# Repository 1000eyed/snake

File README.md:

# Snake

A semi-ortholinear keyboard with LEDs, rotary encoder support and spacebar options.

## How to build one

Very easy project.

### Part list
| #     | name                 | comments                                  |
|-------|----------------------|-------------------------------------------|
| 1     | main PCB             | Order at fabricator of your choice (ouch, expensive!)        |
| 42    | hotswap sockets      | Whatever you are into                 |
| 42    | switches             | MX compatible                        |
| 42    | Keycaps              | MX-compatible                         |
| 1     | Rotary Encoder       | optional                             |
| NA    | Rubber cord D3.53 mm |  https://www.amazon.de/-/en/SHOCRE-Rubber-Gasket-Nitrile-Diameter/dp/B0CGDMGRZM      |

- Solder the sockets to the PCB according to chosen layout. 
- Mount stabilizers. Note: depending on the layout you [i]may[/i] need to file just a tad the stabilizer lips, so they clear the diodes. If they do not seem to fit, do not force them into place, inspect and file if needed!
- Mount the plate to the PCB and secure it with switches in the corners. 
- Mount all other switches.
- Cut and insert cord pieces into the pockets between the PCB and the plate.
- Insert the assembly into the case. Start with the USB side.

### Firmware

- Install WinUSB driver, using Zadig (https://github.com/qmk/qmk_firmware/blob/master/docs/driver_installation_zadig.md)
- Flash the firmware onto the board. Bootloader mode: hold top left key while plugging in. I used QMK Toolbox (https://qmk.fm/toolbox).

### Done

Enjoy your Snake!

## Acknowledgements

Joe Scotto for publishing the STM32 Scottomodule (https://www.youtube.com/joe_scotto). 
Theycallmeboxy for case inspirations (https://github.com/theycallmeboxy/bassik).

## Gallery

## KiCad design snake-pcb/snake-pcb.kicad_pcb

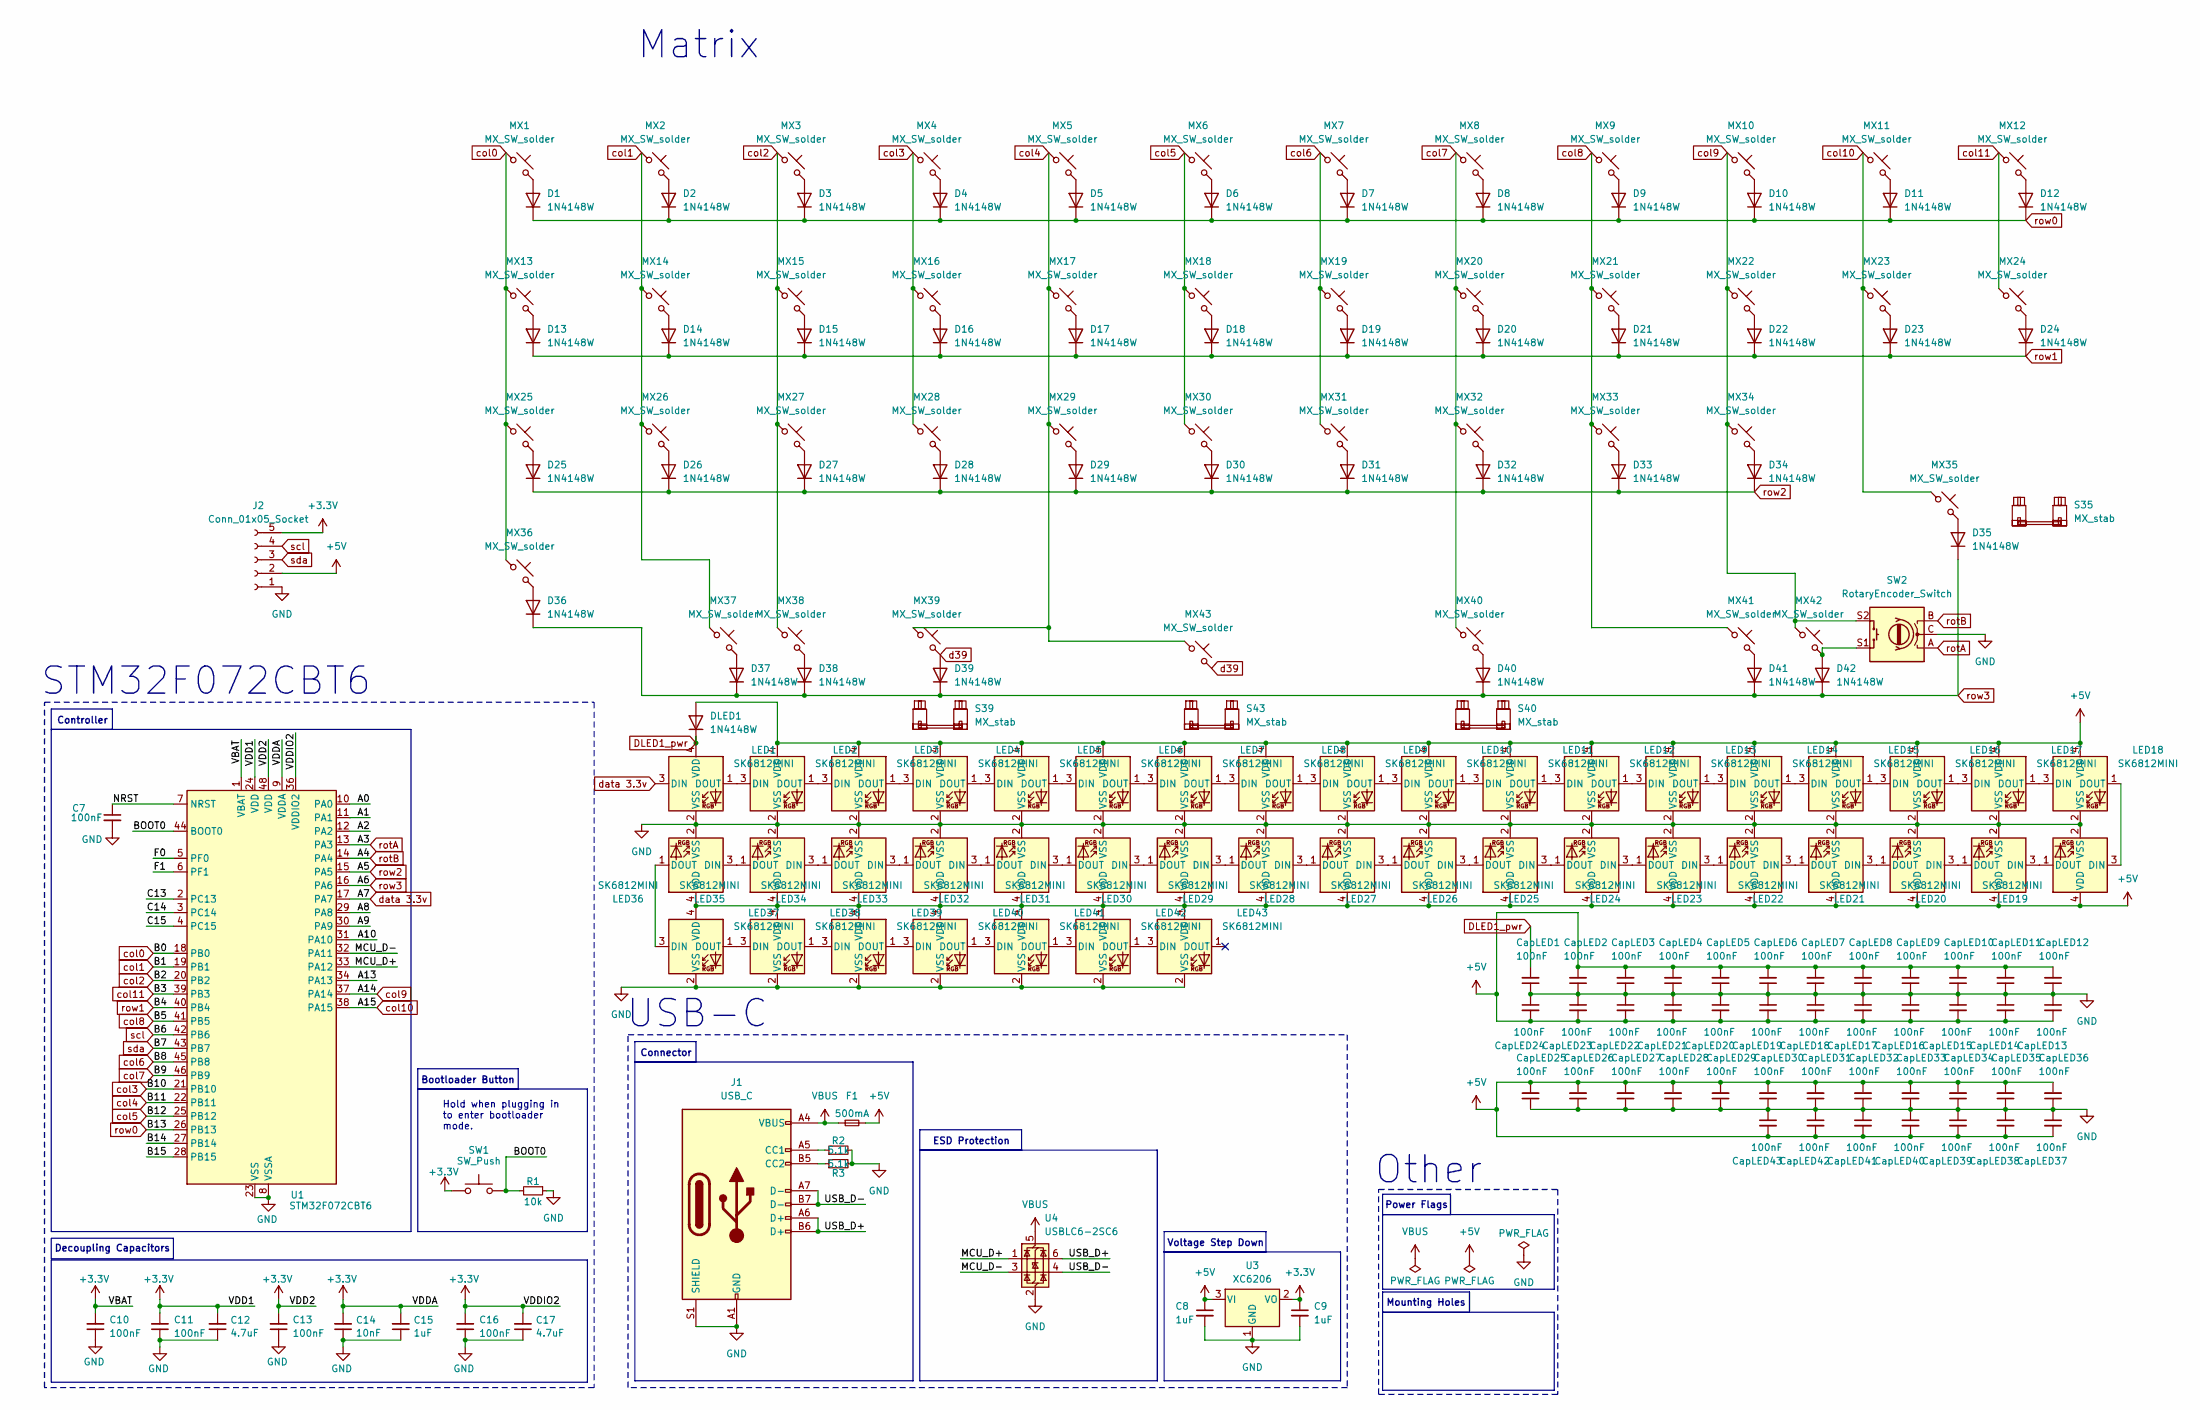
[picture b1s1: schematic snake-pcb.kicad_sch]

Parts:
C7: 100nF; Capacitor_0402; LCSC C307331
C8, C9: 1uF; Capacitor_0402; LCSC C52923
C10, C11, C13, C16: 100nF; Capacitor_0402; MPN CL05B104KB54PNC; LCSC C307331
C12, C17: 4.7uF; Capacitor_0402; MPN CL05A475MP5NRNC; LCSC C23733
C14: 10nF; Capacitor_0402; MPN CL05B103KB5NNNC; LCSC C15195
C15: 1uF; Capacitor_0402; MPN CL05A105KA5NQNC; LCSC C52923
CapLED1, CapLED2, CapLED3, CapLED4, CapLED5, CapLED6, CapLED7, CapLED8, CapLED9, CapLED10, CapLED11, CapLED12, CapLED13, CapLED14, CapLED15, CapLED16, CapLED17, CapLED18, CapLED19, CapLED20, CapLED21, CapLED22, CapLED23, CapLED24, CapLED25, CapLED26, CapLED27, CapLED28, CapLED29, CapLED30, CapLED31, CapLED32, CapLED33, CapLED34, CapLED35, CapLED36, CapLED37, CapLED38, CapLED39, CapLED40, CapLED41, CapLED42, CapLED43: 100nF; Capacitor_0402; MPN CL05B104KB54PNC; LCSC C307331
D1, D2, D3, D4, D5, D6, D7, D8, D9, D10, D11, D12, D13, D14, D15, D16, D17, D18, D19, D20, D21, D22, D23, D24, D25, D26, D27, D28, D29, D30, D31, D32, D33, D34, D35, D36, D37, D38, D39, D40, D41, D42: 1N4148W; D_SOD-123
DLED1: 1N4148W; D_SOD-123
F1: 500mA; Fuse_0603; LCSC C210357
J1: USB_C; USB_C_HRO_TYPE-C-31-M-12; LCSC C165948
J2: Conn_01x05_Socket; JST_EH_B5B-EH-A_1x05_P2.50mm_Vertical
LED1, LED2, LED3, LED4, LED5, LED6, LED7, LED8, LED9, LED10, LED11, LED12, LED13, LED14, LED15, LED16, LED17, LED18, LED19, LED20, LED21, LED22, LED23, LED24, LED25, LED26, LED27, LED28, LED29, LED30, LED31, LED32, LED33, LED34, LED35, LED36, LED37, LED38, LED39, LED40, LED41, LED42, LED43: SK6812MINI; LED_SK6812MINI
MX1, MX2, MX3, MX4, MX5, MX6, MX7, MX8, MX9, MX10, MX11, MX12, MX13, MX14, MX15, MX16, MX17, MX18, MX19, MX20, MX21, MX22, MX23, MX24, MX25, MX26, MX27, MX28, MX29, MX30, MX31, MX32, MX33, MX34, MX35, MX37, MX38, MX39, MX40, MX41, MX42, MX43: MX_SW_solder; SW_MX_HS_CPG151101S11_1u
MX36: MX_SW_solder; SW_MX_HS_CPG151101S11_1.25u
R1: 10k; Resistor_0402; LCSC C25744
R2, R3: 5.1k; Resistor_0402; LCSC C25905
S35: MX_stab; STAB_MX_P_ISO-ROT
S39: MX_stab; STAB_MX_P_2.75u
S40: MX_stab; STAB_MX_P_2.25u
S43: MX_stab; STAB_MX_P_7u
SW1: SW_Push; Button_TL3342; LCSC C115351
SW2: RotaryEncoder_Switch; Encoder_EC11_MX
U1: STM32F072CBT6; Package_LQFP-48_7x7mm_P0.5; LCSC C81720
U3: XC6206; Voltage_SOT-23; LCSC C5446
U4: USBLC6-2SC6; ESD_SOT-23-6; LCSC C2827654

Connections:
+3.3V: C9.1, C10.2, C11.2, C12.2, C13.2, C14.2, C15.2, C16.2, C17.2, J2.5, SW1.1, U1.1 (VBAT), U1.9 (VDDA), U1.24 (VDD), U1.36 (VDDIO2), U1.48 (VDD), U3.2 (VO)
+5V: C8.1, CapLED2.2, CapLED3.2, CapLED4.2, CapLED5.2, CapLED6.2, CapLED7.2, CapLED8.2, CapLED9.2, CapLED10.2, CapLED11.2, CapLED12.2, CapLED13.2, CapLED14.2, CapLED15.2, CapLED16.2, CapLED17.2, CapLED18.2, CapLED19.2, CapLED20.2, CapLED21.2, CapLED22.2, CapLED23.2, CapLED24.2, CapLED25.2, CapLED26.2, CapLED27.2, CapLED28.2, CapLED29.2, CapLED30.2, CapLED31.2, CapLED32.2, CapLED33.2, CapLED34.2, CapLED35.2, CapLED36.2, CapLED37.2, CapLED38.2, CapLED39.2, CapLED40.2, CapLED41.2, CapLED42.2, CapLED43.2, DLED1.2 (A), F1.2, J2.2, LED2.4 (VDD), LED3.4 (VDD), LED4.4 (VDD), LED5.4 (VDD), LED6.4 (VDD), LED7.4 (VDD), LED8.4 (VDD), LED9.4 (VDD), LED10.4 (VDD), LED11.4 (VDD), LED12.4 (VDD), LED13.4 (VDD), LED14.4 (VDD), LED15.4 (VDD), LED16.4 (VDD), LED17.4 (VDD), LED18.4 (VDD), LED19.4 (VDD), LED20.4 (VDD), LED21.4 (VDD), LED22.4 (VDD), LED23.4 (VDD), LED24.4 (VDD), LED25.4 (VDD), LED26.4 (VDD), LED27.4 (VDD), LED28.4 (VDD), LED29.4 (VDD), LED30.4 (VDD), LED31.4 (VDD), LED32.4 (VDD), LED33.4 (VDD), LED34.4 (VDD), LED35.4 (VDD), LED36.4 (VDD), LED37.4 (VDD), LED38.4 (VDD), LED39.4 (VDD), LED40.4 (VDD), LED41.4 (VDD), LED42.4 (VDD), LED43.4 (VDD), U3.3 (VI)
/A0: U1.10 (PA0)
/A1: U1.11 (PA1)
/A2: U1.12 (PA2)
/A8: U1.29 (PA8)
/A9: U1.30 (PA9)
/A10: U1.31 (PA10)
/A13: U1.34 (PA13)
/B14: U1.27 (PB14)
/B15: U1.28 (PB15)
/BOOT0: R1.2, SW1.2, U1.44 (BOOT0)
/C13: U1.2 (PC13)
/C14: U1.3 (PC14)
/C15: U1.4 (PC15)
/F0: U1.5 (PF0)
/F1: U1.6 (PF1)
/MCU_D+: U1.33 (PA12), U4.1 (I/O1)
/MCU_D-: U1.32 (PA11), U4.3 (I/O2)
/NRST: C7.1, U1.7 (NRST)
/USB_D+: J1.A6 (D+), J1.B6 (D+), U4.6 (I/O1)
/USB_D-: J1.A7 (D-), J1.B7 (D-), U4.4 (I/O2)
DLED1_pwr: CapLED1.2, DLED1.1 (K), LED1.4 (VDD)
GND: C7.2, C8.2, C9.2, C10.1, C11.1, C12.1, C13.1, C14.1, C15.1, C16.1, C17.1, CapLED1.1, CapLED2.1, CapLED3.1, CapLED4.1, CapLED5.1, CapLED6.1, CapLED7.1, CapLED8.1, CapLED9.1, CapLED10.1, CapLED11.1, CapLED12.1, CapLED13.1, CapLED14.1, CapLED15.1, CapLED16.1, CapLED17.1, CapLED18.1, CapLED19.1, CapLED20.1, CapLED21.1, CapLED22.1, CapLED23.1, CapLED24.1, CapLED25.1, CapLED26.1, CapLED27.1, CapLED28.1, CapLED29.1, CapLED30.1, CapLED31.1, CapLED32.1, CapLED33.1, CapLED34.1, CapLED35.1, CapLED36.1, CapLED37.1, CapLED38.1, CapLED39.1, CapLED40.1, CapLED41.1, CapLED42.1, CapLED43.1, J1.A1 (GND), J1.A12 (GND), J1.B1 (GND), J1.B12 (GND), J1.S1 (SHIELD), J2.1, LED1.2 (VSS), LED2.2 (VSS), LED3.2 (VSS), LED4.2 (VSS), LED5.2 (VSS), LED6.2 (VSS), LED7.2 (VSS), LED8.2 (VSS), LED9.2 (VSS), LED10.2 (VSS), LED11.2 (VSS), LED12.2 (VSS), LED13.2 (VSS), LED14.2 (VSS), LED15.2 (VSS), LED16.2 (VSS), LED17.2 (VSS), LED18.2 (VSS), LED19.2 (VSS), LED20.2 (VSS), LED21.2 (VSS), LED22.2 (VSS), LED23.2 (VSS), LED24.2 (VSS), LED25.2 (VSS), LED26.2 (VSS), LED27.2 (VSS), LED28.2 (VSS), LED29.2 (VSS), LED30.2 (VSS), LED31.2 (VSS), LED32.2 (VSS), LED33.2 (VSS), LED34.2 (VSS), LED35.2 (VSS), LED36.2 (VSS), LED37.2 (VSS), LED38.2 (VSS), LED39.2 (VSS), LED40.2 (VSS), LED41.2 (VSS), LED42.2 (VSS), LED43.2 (VSS), R1.1, R2.2, R3.2, SW2.C, U1.8 (VSSA), U1.23 (VSS), U1.35 (VSS), U1.47 (VSS), U3.1 (GND), U4.2 (GND)
unnamed: D1.2 (A), MX1.2
unnamed: D2.2 (A), MX2.2
unnamed: D3.2 (A), MX3.2
unnamed: D4.2 (A), MX4.2
unnamed: D5.2 (A), MX5.2
unnamed: D6.2 (A), MX6.2
unnamed: D7.2 (A), MX7.2
unnamed: D8.2 (A), MX8.2
unnamed: D9.2 (A), MX9.2
unnamed: D10.2 (A), MX10.2
unnamed: D11.2 (A), MX11.2
unnamed: D12.2 (A), MX12.2
unnamed: D13.2 (A), MX13.2
unnamed: D14.2 (A), MX14.2
unnamed: D15.2 (A), MX15.2
unnamed: D16.2 (A), MX16.2
unnamed: D17.2 (A), MX17.2
unnamed: D18.2 (A), MX18.2
unnamed: D19.2 (A), MX19.2
unnamed: D20.2 (A), MX20.2
unnamed: D21.2 (A), MX21.2
unnamed: D22.2 (A), MX22.2
unnamed: D23.2 (A), MX23.2
unnamed: D24.2 (A), MX24.2
unnamed: D25.2 (A), MX25.2
unnamed: D26.2 (A), MX26.2
unnamed: D27.2 (A), MX27.2
unnamed: D28.2 (A), MX28.2
unnamed: D29.2 (A), MX29.2
unnamed: D30.2 (A), MX30.2
unnamed: D31.2 (A), MX31.2
unnamed: D32.2 (A), MX32.2
unnamed: D33.2 (A), MX33.2
unnamed: D34.2 (A), MX34.2
unnamed: D35.2 (A), MX35.2
unnamed: D36.2 (A), MX36.2
unnamed: D37.2 (A), MX37.2
unnamed: D38.2 (A), MX38.2
unnamed: D40.2 (A), MX40.2
unnamed: D41.2 (A), MX41.2
unnamed: D42.2 (A), MX42.2, SW2.S1
unnamed: J1.A5 (CC1), R2.1
unnamed: J1.B5 (CC2), R3.1
unnamed: LED1.1 (DOUT), LED2.3 (DIN)
unnamed: LED2.1 (DOUT), LED3.3 (DIN)
unnamed: LED3.1 (DOUT), LED4.3 (DIN)
unnamed: LED4.1 (DOUT), LED5.3 (DIN)
unnamed: LED5.1 (DOUT), LED6.3 (DIN)
unnamed: LED6.1 (DOUT), LED7.3 (DIN)
unnamed: LED7.1 (DOUT), LED8.3 (DIN)
unnamed: LED8.1 (DOUT), LED9.3 (DIN)
unnamed: LED9.1 (DOUT), LED10.3 (DIN)
unnamed: LED10.1 (DOUT), LED11.3 (DIN)
unnamed: LED11.1 (DOUT), LED12.3 (DIN)
unnamed: LED12.1 (DOUT), LED13.3 (DIN)
unnamed: LED13.1 (DOUT), LED14.3 (DIN)
unnamed: LED14.1 (DOUT), LED15.3 (DIN)
unnamed: LED15.1 (DOUT), LED16.3 (DIN)
unnamed: LED16.1 (DOUT), LED17.3 (DIN)
unnamed: LED17.1 (DOUT), LED18.3 (DIN)
unnamed: LED18.1 (DOUT), LED19.3 (DIN)
unnamed: LED19.1 (DOUT), LED20.3 (DIN)
unnamed: LED20.1 (DOUT), LED21.3 (DIN)
unnamed: LED21.1 (DOUT), LED22.3 (DIN)
unnamed: LED22.1 (DOUT), LED23.3 (DIN)
unnamed: LED23.1 (DOUT), LED24.3 (DIN)
unnamed: LED24.1 (DOUT), LED25.3 (DIN)
unnamed: LED25.1 (DOUT), LED26.3 (DIN)
unnamed: LED26.1 (DOUT), LED27.3 (DIN)
unnamed: LED27.1 (DOUT), LED28.3 (DIN)
unnamed: LED28.1 (DOUT), LED29.3 (DIN)
unnamed: LED29.1 (DOUT), LED30.3 (DIN)
unnamed: LED30.1 (DOUT), LED31.3 (DIN)
unnamed: LED31.1 (DOUT), LED32.3 (DIN)
unnamed: LED32.1 (DOUT), LED33.3 (DIN)
unnamed: LED33.1 (DOUT), LED34.3 (DIN)
unnamed: LED34.1 (DOUT), LED35.3 (DIN)
unnamed: LED35.1 (DOUT), LED36.3 (DIN)
unnamed: LED36.1 (DOUT), LED37.3 (DIN)
unnamed: LED37.1 (DOUT), LED38.3 (DIN)
unnamed: LED38.1 (DOUT), LED39.3 (DIN)
unnamed: LED39.1 (DOUT), LED40.3 (DIN)
unnamed: LED40.1 (DOUT), LED41.3 (DIN)
unnamed: LED41.1 (DOUT), LED42.3 (DIN)
unnamed: LED42.1 (DOUT), LED43.3 (DIN)
VBUS: F1.1, J1.A4 (VBUS), J1.A9 (VBUS), J1.B4 (VBUS), J1.B9 (VBUS), U4.5 (VBUS)
col0: MX1.1, MX13.1, MX25.1, MX36.1, U1.18 (PB0)
col1: MX2.1, MX14.1, MX26.1, MX37.1, U1.19 (PB1)
col2: MX3.1, MX15.1, MX27.1, MX38.1, U1.20 (PB2)
col3: MX4.1, MX16.1, MX28.1, U1.21 (PB10)
col4: MX5.1, MX17.1, MX29.1, MX39.1, MX43.1, U1.22 (PB11)
col5: MX6.1, MX18.1, MX30.1, U1.25 (PB12)
col6: MX7.1, MX19.1, MX31.1, U1.45 (PB8)
col7: MX8.1, MX20.1, MX32.1, MX40.1, U1.46 (PB9)
col8: MX9.1, MX21.1, MX33.1, MX41.1, U1.41 (PB5)
col9: MX10.1, MX22.1, MX34.1, MX42.1, SW2.S2, U1.37 (PA14)
col10: MX11.1, MX23.1, MX35.1, U1.38 (PA15)
col11: MX12.1, MX24.1, U1.39 (PB3)
d39: D39.2 (A), MX39.2, MX43.2
data 3.3v: LED1.3 (DIN), U1.17 (PA7)
rotA: SW2.A, U1.13 (PA3)
rotB: SW2.B, U1.14 (PA4)
row0: D1.1 (K), D2.1 (K), D3.1 (K), D4.1 (K), D5.1 (K), D6.1 (K), D7.1 (K), D8.1 (K), D9.1 (K), D10.1 (K), D11.1 (K), D12.1 (K), U1.26 (PB13)
row1: D13.1 (K), D14.1 (K), D15.1 (K), D16.1 (K), D17.1 (K), D18.1 (K), D19.1 (K), D20.1 (K), D21.1 (K), D22.1 (K), D23.1 (K), D24.1 (K), U1.40 (PB4)
row2: D25.1 (K), D26.1 (K), D27.1 (K), D28.1 (K), D29.1 (K), D30.1 (K), D31.1 (K), D32.1 (K), D33.1 (K), D34.1 (K), U1.15 (PA5)
row3: D35.1 (K), D36.1 (K), D37.1 (K), D38.1 (K), D39.1 (K), D40.1 (K), D41.1 (K), D42.1 (K), U1.16 (PA6)
scl: J2.4, U1.42 (PB6)
sda: J2.3, U1.43 (PB7)

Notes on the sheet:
Hold when plugging in to enter bootloader mode.
STM32F072CBT6
USB-C
Mounting Holes
Decoupling Capacitors
Controller
ESD Protection
Power Flags
Voltage Step Down
Other
Bootloader Button
Matrix
Connector

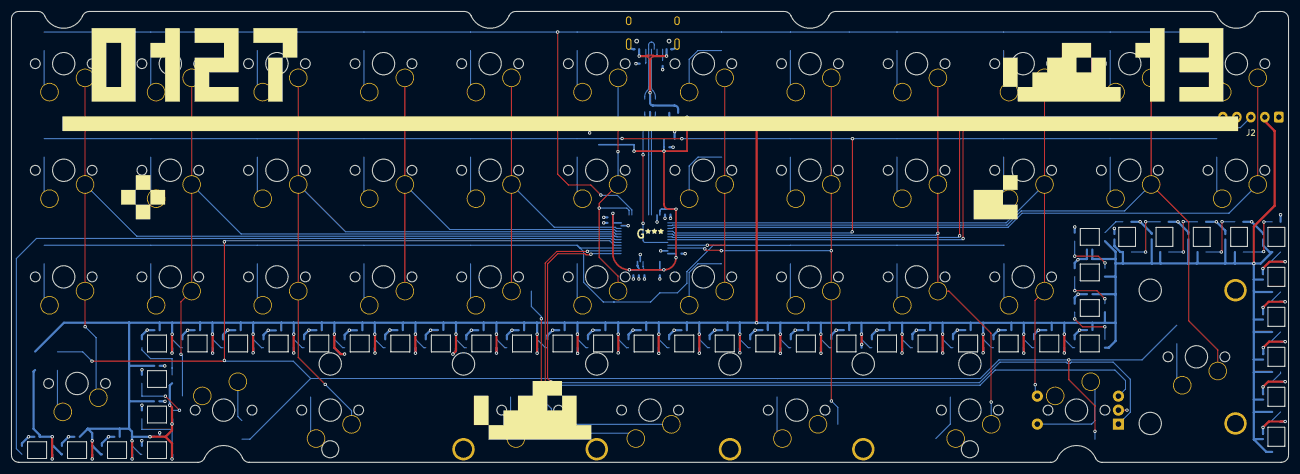
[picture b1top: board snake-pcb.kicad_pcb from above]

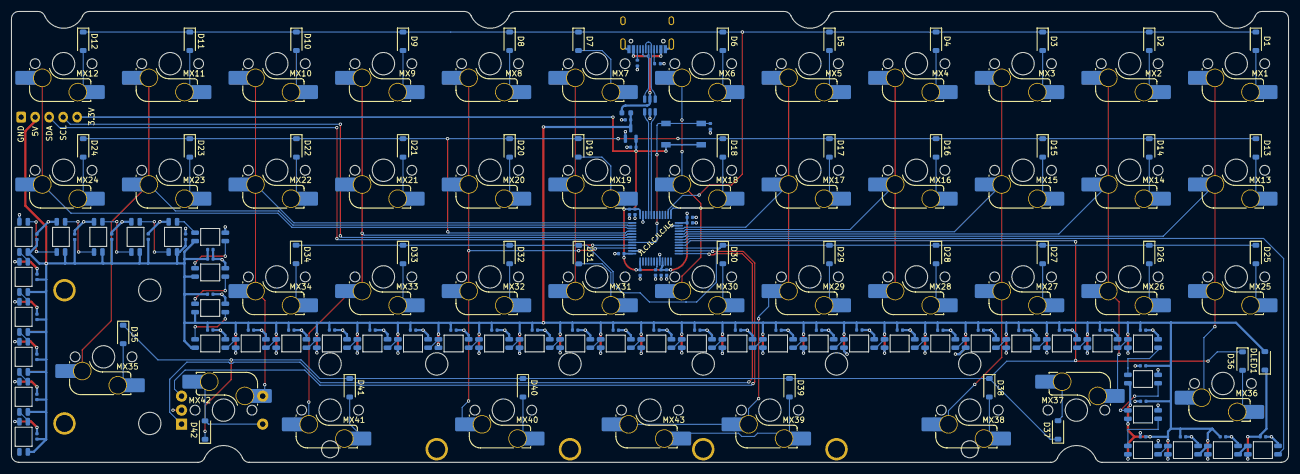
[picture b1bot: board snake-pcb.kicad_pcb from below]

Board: 4 copper layers, 228.2 x 80.6 mm, 198 parts (192 on the bottom side), 118 nets.

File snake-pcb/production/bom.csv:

Designator,Footprint,Quantity,Value,LCSC Part #
"C10, C11, C13, C16, C7, CAPLED1, CAPLED10, CAPLED11, CAPLED12, CAPLED13, CAPLED14, CAPLED15, CAPLED16, CAPLED17, CAPLED18, CAPLED19, CAPLED2, CAPLED20, CAPLED21, CAPLED22, CAPLED23, CAPLED24, CAPLED25, CAPLED26, CAPLED27, CAPLED28, CAPLED29, CAPLED3, CAPLED30, CAPLED31, CAPLED32, CAPLED33, CAPLED34, CAPLED35, CAPLED36, CAPLED37, CAPLED38, CAPLED39, CAPLED4, CAPLED40, CAPLED41, CAPLED42, CAPLED43, CAPLED5, CAPLED6, CAPLED7, CAPLED8, CAPLED9",Capacitor_0402,48,100nF,C307331
"C12, C17",Capacitor_0402,2,4.7uF,C23733
C14,Capacitor_0402,1,10nF,C15195
"C15, C8, C9",Capacitor_0402,3,1uF,C52923
"D1, D10, D11, D12, D13, D14, D15, D16, D17, D18, D19, D2, D20, D21, D22, D23, D24, D25, D26, D27, D28, D29, D3, D30, D31, D32, D33, D34, D35, D36, D37, D38, D39, D4, D40, D41, D42, D5, D6, D7, D8, D9, DLED1",D_SOD-123,43,1N4148W,
F1,Fuse_0603,1,500mA,C210357
J1,USB_C_HRO_TYPE-C-31-M-12,1,USB_C,C165948
J2,JST_EH_B5B-EH-A_1x05_P2.50mm_Vertical,1,Conn_01x05_Socket,
"LED1, LED10, LED11, LED12, LED13, LED14, LED15, LED16, LED17, LED18, LED19, LED2, LED20, LED21, LED22, LED23, LED24, LED25, LED26, LED27, LED28, LED29, LED3, LED30, LED31, LED32, LED33, LED34, LED35, LED36, LED37, LED38, LED39, LED4, LED40, LED41, LED42, LED43, LED5, LED6, LED7, LED8, LED9",LED_SK6812MINI,43,SK6812MINI,
"MX1, MX10, MX11, MX12, MX13, MX14, MX15, MX16, MX17, MX18, MX19, MX2, MX20, MX21, MX22, MX23, MX24, MX25, MX26, MX27, MX28, MX29, MX3, MX30, MX31, MX32, MX33, MX34, MX35, MX37, MX38, MX39, MX4, MX40, MX41, MX42, MX43, MX5, MX6, MX7, MX8, MX9",SW_MX_HS_CPG151101S11_1u,42,MX_SW_solder,
MX36,SW_MX_HS_CPG151101S11_1.25u,1,MX_SW_solder,
R1,Resistor_0402,1,10k,C25744
"R2, R3",Resistor_0402,2,5.1k,C25905
S35,STAB_MX_P_ISO-ROT,1,MX_stab,
S39,STAB_MX_P_2.75u,1,MX_stab,
S40,STAB_MX_P_2.25u,1,MX_stab,
SW1,Button_TL3342,1,SW_Push,C115351
SW2,Encoder_EC11_MX,1,RotaryEncoder_Switch,
U1,Package_LQFP-48_7x7mm_P0.5,1,STM32F072CBT6,C81720
U3,Voltage_SOT-23,1,XC6206,C5446
U4,ESD_SOT-23-6,1,USBLC6-2SC6,C2827654

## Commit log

2024-12-27 pcb almost finished!
2024-12-27 pcb almost ever mo finished!
2024-12-27 gerbers added
2024-12-27 pcb done
2025-01-18 Files ready
2025-01-18 Keymap added
2025-01-22 add vial firmware
2025-01-31 plate changes: added seesaw mount plate, removed faulty plate version STL, 3df file updated.
2025-01-31 faulty plate removed now
